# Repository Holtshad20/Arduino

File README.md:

# Arduino
Projetos Arduino

Estudos, Ensaios e Projetos com Arduino.

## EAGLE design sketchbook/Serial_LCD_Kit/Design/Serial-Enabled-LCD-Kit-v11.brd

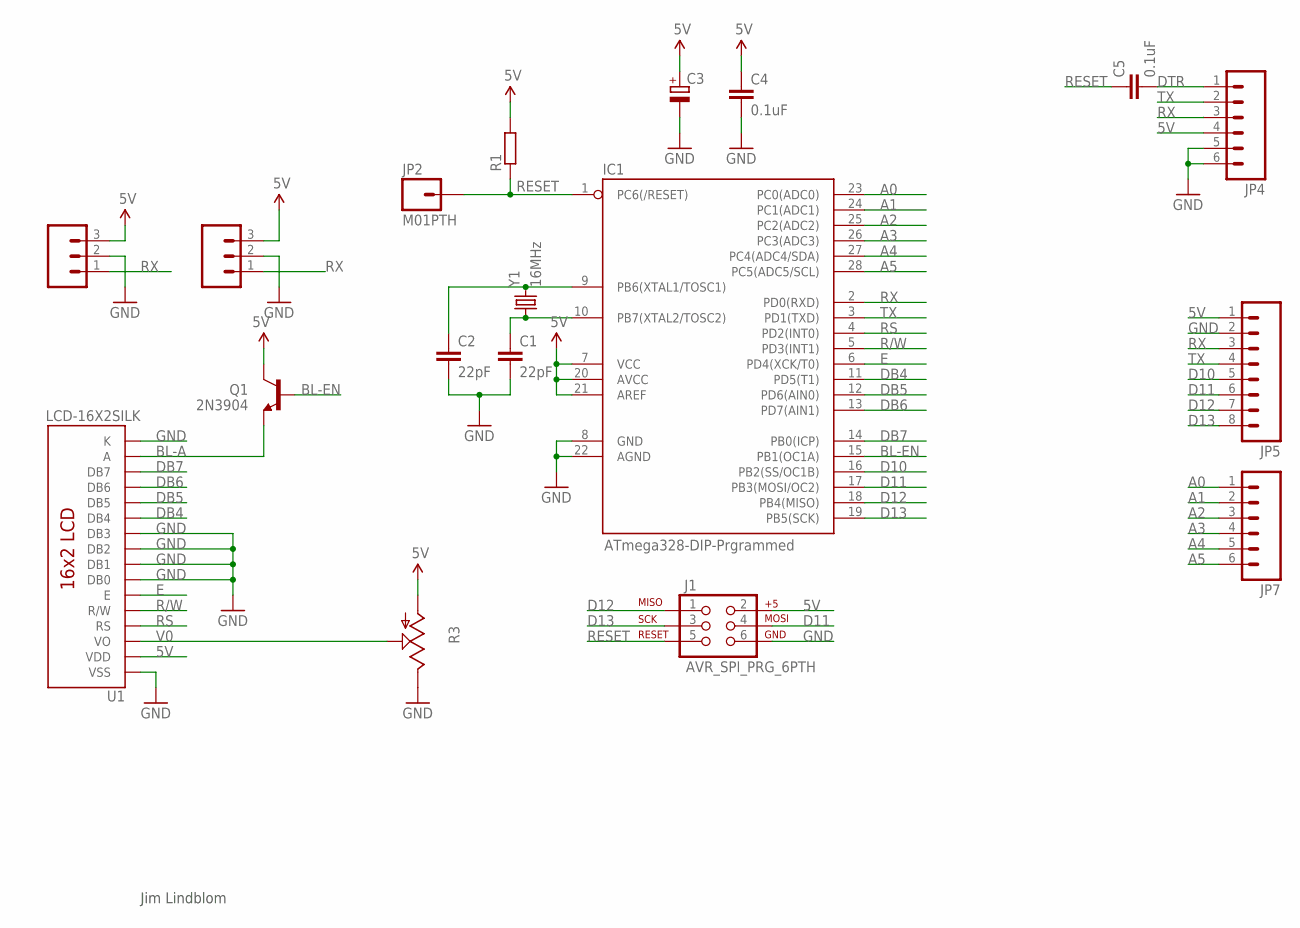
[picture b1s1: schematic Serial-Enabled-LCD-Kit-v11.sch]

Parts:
C1, C2: 22pF; CAP-PTH-SMALL2
C3: CPOL-EUE2-4; E2-4
C4, C5: 0.1uF; CAP-PTH-SMALL2
IC1: ATmega328-DIP-Prgrammed; DIL28-3
J1: AVR_SPI_PRG_6PTH; 2X3
JP1, JP6: M03PTH; 1X03
JP2: M01PTH; 1X01
JP4, JP7: M06SIP; 1X06
JP5: M08; 1X08
Q1: 2N3904; TO-92
R1: R-EU_0207/10; 0207/10
R3: TRIM_US-S64W; S64W
U1: LCD-16X2SILK; LCD-16X2
Y1: 16MHz; HC49US

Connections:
5V: C3.+, C4.1, IC1.7 (VCC), IC1.20 (AVCC), IC1.21 (AREF), J1.2, JP1.3, JP4.4, JP5.1, JP6.3, Q1.3 (C), R1.2, R3.A, U1.2 (VDD)
A0: IC1.23 (PC0(ADC0)), JP7.1
A1: IC1.24 (PC1(ADC1)), JP7.2
A2: IC1.25 (PC2(ADC2)), JP7.3
A3: IC1.26 (PC3(ADC3)), JP7.4
A4: IC1.27 (PC4(ADC4/SDA)), JP7.5
A5: IC1.28 (PC5(ADC5/SCL)), JP7.6
BL-A: Q1.1 (E), U1.15 (A)
BL-EN: IC1.15 (PB1(OC1A)), Q1.2 (B)
D10: IC1.16 (PB2(SS/OC1B)), JP5.5
D11: IC1.17 (PB3(MOSI/OC2)), J1.4, JP5.6
D12: IC1.18 (PB4(MISO)), J1.1, JP5.7
D13: IC1.19 (PB5(SCK)), J1.3, JP5.8
DB4: IC1.11 (PD5(T1)), U1.11 (DB4)
DB5: IC1.12 (PD6(AIN0)), U1.12 (DB5)
DB6: IC1.13 (PD7(AIN1)), U1.13 (DB6)
DB7: IC1.14 (PB0(ICP)), U1.14 (DB7)
DTR: C5.2, JP4.1
E: IC1.6 (PD4(XCK/T0)), U1.6 (E)
GND: C1.2, C2.2, C3.-, C4.2, IC1.8 (GND), IC1.22 (AGND), J1.6, JP1.2, JP4.5, JP4.6, JP5.2, JP6.2, R3.E, U1.1 (VSS), U1.7 (DB0), U1.8 (DB1), U1.9 (DB2), U1.10 (DB3), U1.16 (K)
R/W: IC1.5 (PD3(INT1)), U1.5 (R/W)
RESET: C5.1, IC1.1 (PC6(/RESET)), J1.5, JP2.1, R1.1
RS: IC1.4 (PD2(INT0)), U1.4 (RS)
RX: IC1.2 (PD0(RXD)), JP4.3, JP5.3, JP6.1
TX: IC1.3 (PD1(TXD)), JP4.2, JP5.4
V0: R3.S, U1.3 (VO)
XTAL1: C2.1, IC1.9 (PB6(XTAL1/TOSC1)), Y1.2
XTAL2: C1.1, IC1.10 (PB7(XTAL2/TOSC2)), Y1.1

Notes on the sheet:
Jim Lindblom

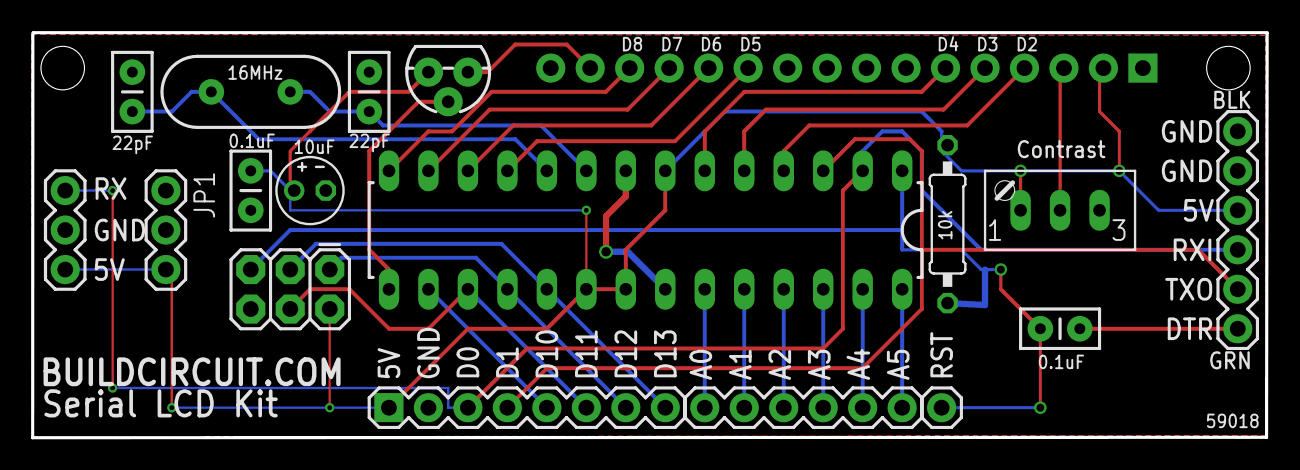
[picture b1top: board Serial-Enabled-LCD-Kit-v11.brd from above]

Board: 2 copper layers, 79.4 x 26.1 mm, 18 parts (1 on the bottom side), 28 nets.

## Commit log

2015-06-09 Projetos Arduino
2016-06-10 atualizei
2018-11-27 Update LiquidCrytal595.cpp
    Have to add (line 295) a return 0; There's the explanation.
2019-07-17 Update LiquidCrystal595.cpp
    Correction on comment in line 295
